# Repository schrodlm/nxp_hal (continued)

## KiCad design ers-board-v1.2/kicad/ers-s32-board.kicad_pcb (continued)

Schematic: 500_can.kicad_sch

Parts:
C30: 10uF; C_0805_2012Metric_Pad1.18x1.45mm_HandSolder; JLCPCB Part C15850
C31, C32: 100nF; C_0603_1608Metric_Pad1.08x0.95mm_HandSolder; JLCPCB Part C14663
C33, C34: 100pF; C_0603_1608Metric_Pad1.08x0.95mm_HandSolder; JLCPCB Part C14858
D4: PESD2IVN24-TR; SOT-23; Mouser 771-PESD2IVN24-TR
L2: DLW21SZ900HQ2L; L_choke_DLW21SZ; Mouser 81-DLW21SZ900HQ2L
U2: TJA1044GTK/3Z; HVSON-8-1EP_3x3mm_P0.65mm_EP1.6x2.4mm; Mouser 771-TJA1044GTK/3Z

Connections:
/CAN_S32_+: C34.1, D4.1, L2.2; also elsewhere on the board
/CAN_S32_-: C33.1, D4.2, L2.3; also elsewhere on the board
/CAN_S32_RX: U2.4 (RXD); also elsewhere on the board
/CAN_S32_STB: U2.8 (STB); also elsewhere on the board
/CAN_S32_TX: U2.1 (TXD); also elsewhere on the board
GND: C30.2, C31.2, C32.2, C33.2, C34.2, D4.3, U2.2 (GND), U2.9 (EP); also elsewhere on the board
unnamed: L2.1, U2.7 (CANH)
unnamed: L2.4, U2.6 (CANL)
VCC_3V3_CTRL: C32.1, U2.5 (VIO); also elsewhere on the board
VCC_5V_CTRL: C30.1, C31.1, U2.3 (VCC); also elsewhere on the board

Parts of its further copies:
C35: 10uF; C_0805_2012Metric_Pad1.18x1.45mm_HandSolder; JLCPCB Part C15850
C36, C37: 100nF; C_0603_1608Metric_Pad1.08x0.95mm_HandSolder; JLCPCB Part C14663
C38, C39: 100pF; C_0603_1608Metric_Pad1.08x0.95mm_HandSolder; JLCPCB Part C14858
D5: PESD2IVN24-TR; SOT-23; Mouser 771-PESD2IVN24-TR
L3: DLW21SZ900HQ2L; L_choke_DLW21SZ; Mouser 81-DLW21SZ900HQ2L
U3: TJA1044GTK/3Z; HVSON-8-1EP_3x3mm_P0.65mm_EP1.6x2.4mm; Mouser 771-TJA1044GTK/3Z

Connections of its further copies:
/CAN_STM_+: C39.1, D5.1, L3.2; also elsewhere on the board
/CAN_STM_-: C38.1, D5.2, L3.3; also elsewhere on the board
/CAN_STM_RX: U3.4 (RXD); also elsewhere on the board
/CAN_STM_STB: U3.8 (STB); also elsewhere on the board
/CAN_STM_TX: U3.1 (TXD); also elsewhere on the board
GND: C35.2, C36.2, C37.2, C38.2, C39.2, D5.3, U3.2 (GND), U3.9 (EP); also elsewhere on the board
unnamed: L3.1, U3.7 (CANH)
unnamed: L3.4, U3.6 (CANL)
VCC_3V3_DISCO: C37.1, U3.5 (VIO); also elsewhere on the board
VCC_5V_DISCO: C35.1, C36.1, U3.3 (VCC); also elsewhere on the board

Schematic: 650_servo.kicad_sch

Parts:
C43: 10uF; C_0805_2012Metric_Pad1.18x1.45mm_HandSolder; JLCPCB Part C15850
J11: SERVO; PinHeader_1x03_P2.54mm_Vertical; JLCPCB Part C2937625

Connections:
/SERVO_PWM: J11.1; also elsewhere on the board
GND: C43.2, J11.3; also elsewhere on the board
VCC_5V_PERIPH: C43.1, J11.2; also elsewhere on the board

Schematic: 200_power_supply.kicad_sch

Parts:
C4, C6: 10uF; C_0805_2012Metric_Pad1.18x1.45mm_HandSolder; JLCPCB Part C15850
C5, C7: 100nF; C_0603_1608Metric_Pad1.08x0.95mm_HandSolder; JLCPCB Part C14663
FB2: BLM18KG601SN1D; L_0603_1608Metric_Pad1.05x0.95mm_HandSolder; JLCPCB Part C85833
U1: TPS70933QDRV; WSON-6-1EP_2x2mm_P0.65mm_EP1x1.6mm; Mouser 595-TPS70933QDRVRQ1

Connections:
/200_power_supply/VCC_3V3_LDO: C6.1, C7.1, FB2.1, U1.1 (OUT)
GND: C4.2, C5.2, C6.2, C7.2, U1.3 (GND), U1.7 (GND); also elsewhere on the board
VCC_3V3: FB2.2; also elsewhere on the board
VCC_5V: C4.1, C5.1, U1.4 (EN), U1.6 (IN); also elsewhere on the board

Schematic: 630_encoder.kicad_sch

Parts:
C41, C42: 10nF; C_0603_1608Metric_Pad1.08x0.95mm_HandSolder; JLCPCB Part C57112
IC4: PEC12R-4220F-S0024; Mouser 652-PEC12R-4220F-S24
R30, R31, R32, R33, R34: 10k; R_0603_1608Metric_Pad0.98x0.95mm_HandSolder; JLCPCB Part C25804

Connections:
/ENC_A: C42.1, R31.2; also elsewhere on the board
/ENC_B: C41.1, R30.2; also elsewhere on the board
/ENC_SWITCH: IC4.S2, R34.1; also elsewhere on the board
GND: C41.2, C42.2, IC4.MP, R32.2, R33.2, R34.2; also elsewhere on the board
unnamed: IC4.A, R31.1, R32.1
unnamed: IC4.B, R30.1, R33.1
VCC_3V3_PERIPH: IC4.C, IC4.S1; also elsewhere on the board

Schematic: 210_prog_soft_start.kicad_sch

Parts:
C3: 100nF; C_0603_1608Metric_Pad1.08x0.95mm_HandSolder; JLCPCB Part C14663
D3: B5817WS; D_SOD-323; Mouser 771-PMEG4005EJ-T/R
Q1: DMG3406L; SOT-23; Mouser 621-DMG3406L-13
R9: 10k; R_0603_1608Metric_Pad0.98x0.95mm_HandSolder; Mouser 603-RC0603FR-0710KL; not fitted
R10: 10k; R_0603_1608Metric_Pad0.98x0.95mm_HandSolder; JLCPCB Part C25804

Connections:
/210_prog_soft_start/PROG_SOFT_START_GATE: C3.1, D3.2 (A), Q1.1 (G), R10.1
/PROG_USB_VBUS: D3.1 (K), R9.2, R10.2; also elsewhere on the board
/VCC_3V3_PROG_RAW: Q1.3 (D); also elsewhere on the board
GND: C3.2, R9.1; also elsewhere on the board
VCC_3V3_PROG: Q1.2 (S); also elsewhere on the board

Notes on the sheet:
This implements soft-start and disconnects VCC_3V3_SOFT if not powered by USB_VBUS (5V).
This does not seem to be needed because even the VBUS from USB does not go to 0 immediately.

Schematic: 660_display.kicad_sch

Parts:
J12: DISPLAY; PinHeader_1x08_P2.54mm_Vertical; JLCPCB Part C492407

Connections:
/MEM_DISP_SCK: J12.4; also elsewhere on the board
/MEM_DISP_SDI: J12.3; also elsewhere on the board
/~DISP_CS: J12.6; also elsewhere on the board
/~DISP_DC: J12.5; also elsewhere on the board
/~DISP_RST: J12.7; also elsewhere on the board
GND: J12.1, J12.8; also elsewhere on the board
VCC_3V3_PERIPH: J12.2; also elsewhere on the board

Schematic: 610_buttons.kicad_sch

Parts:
R24, R25, R26, R27: 10k; R_0603_1608Metric_Pad0.98x0.95mm_HandSolder; JLCPCB Part C25804
S2, S3, S4, S5: PTS815SJM250SMTR_LFS; Mouser 611-PTS815SJM250SMTR

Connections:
/BTN_1: R27.1, S2.2; also elsewhere on the board
/BTN_2: R26.1, S3.2; also elsewhere on the board
/BTN_3: R25.1, S4.2; also elsewhere on the board
/BTN_4: R24.1, S5.2; also elsewhere on the board
GND: R24.2, R25.2, R26.2, R27.2; also elsewhere on the board
VCC_3V3_PERIPH: S2.1, S3.1, S4.1, S5.1; also elsewhere on the board

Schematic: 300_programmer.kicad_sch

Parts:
C8: 10uF; C_0805_2012Metric_Pad1.18x1.45mm_HandSolder; JLCPCB Part C15850
C9, C19: 22uF; C_0805_2012Metric_Pad1.18x1.45mm_HandSolder; JLCPCB Part C45783
C10, C11, C12, C13, C14, C15, C16, C17: 100nF; C_0603_1608Metric_Pad1.08x0.95mm_HandSolder; JLCPCB Part C14663
C18: 47pF; C_0603_1608Metric_Pad1.08x0.95mm_HandSolder; JLCPCB Part C1671
C20, C21: 8pF; C_0603_1608Metric_Pad1.08x0.95mm_HandSolder; JLCPCB Part C36508
IC1: LPC55S69JBD64K; Mouser 771-LPC55S69JBD64K
L1: 4u7H; LCD0805; JLCPCB Part C395016
R11, R12: 10k; R_0603_1608Metric_Pad0.98x0.95mm_HandSolder; Mouser 603-RC0603FR-0710KL; not fitted
R13, R14: 0R; R_0603_1608Metric_Pad0.98x0.95mm_HandSolder; Mouser 603-RC0603FR-100RL; not fitted
Y1: 3225-16-8-10-10/A; 3225-16-8-10-10_A; JLCPCB Part C2981656

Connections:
/300_programmer/CLK_N: C20.1, IC1.19 (XTAL32M_N), Y1.1
/300_programmer/CLK_P: C21.1, IC1.20 (XTAL32M_P), Y1.3
/300_programmer/HW_VER_6: IC1.38 (PIO0_18/ACMP0_C), R11.2, R13.1
/300_programmer/HW_VER_7: IC1.18 (PIO0_27), R12.2, R14.1
/300_programmer/USB1_VBUS: IC1.25 (USB1_VBUS); also elsewhere on the board
/PROG_ISP_EN_LED_CTRL: IC1.56 (PIO0_5/TDI); also elsewhere on the board
/PROG_RESETN: IC1.21 (RESETN); also elsewhere on the board
/PROG_SWCLK: IC1.6 (PIO0_11/ADC0_9); also elsewhere on the board
/PROG_SWDIO: IC1.5 (PIO0_12/ADC0_10); also elsewhere on the board
/PROG_SWO: IC1.13 (PIO0_10/ADC0_1); also elsewhere on the board
/PROG_USB_D+: IC1.23 (USB1_DP); also elsewhere on the board
/PROG_USB_D-: IC1.24 (USB1_DM); also elsewhere on the board
/TARGET_DEBUG_RX: IC1.51 (PIO0_25); also elsewhere on the board
/TARGET_DEBUG_TX: IC1.45 (PIO0_24); also elsewhere on the board
/TARGET_RESETN: IC1.58 (PIO0_19); also elsewhere on the board
/TARGET_SWCLK: IC1.36 (PIO0_0/ACMP0_A); also elsewhere on the board
/TARGET_SWDIO: IC1.52 (PIO0_2/TRST); also elsewhere on the board
/TARGET_SWO: IC1.53 (PIO0_3/TCK); also elsewhere on the board
GND: C8.2, C9.2, C10.2, C11.2, C12.2, C13.2, C14.2, C15.2, C16.2, C17.2, C18.2, C19.2, C20.2, C21.2, IC1.11 (VSSA), IC1.22 (USB1_VSS), IC1.26 (USB1_VSS), IC1.30 (VSS_DCDC), IC1.37 (PIO0_9/ACMP0_B), IC1.64 (USB0_VSS), IC1.65 (EP), R13.2, R14.2, Y1.2, Y1.4; also elsewhere on the board
unnamed: C19.1, IC1.28 (VDD_PMU), IC1.29 (FB), L1.1
unnamed: IC1.31 (LX), L1.2
VCC_3V3_PROG: C8.1, C9.1, C10.1, C11.1, C12.1, C13.1, C14.1, C15.1, C16.1, C17.1, C18.1, IC1.8 (VDD), IC1.9 (VDDA), IC1.10 (VREFP), IC1.15 (PIO0_31/ADC0_3), IC1.16 (VDD), IC1.27 (USB1_3V3), IC1.32 (VBAT_DCDC), IC1.33 (VBAT_PMU), IC1.43 (VDD), IC1.54 (VDD), IC1.61 (USB0_3V3), R11.1, R12.1; also elsewhere on the board

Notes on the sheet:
Connect to GND: Disable second VCOM
SWD debug disabled when low Presumably has internal pull-up
VCOM disabled when low Presumably has internal pull-up

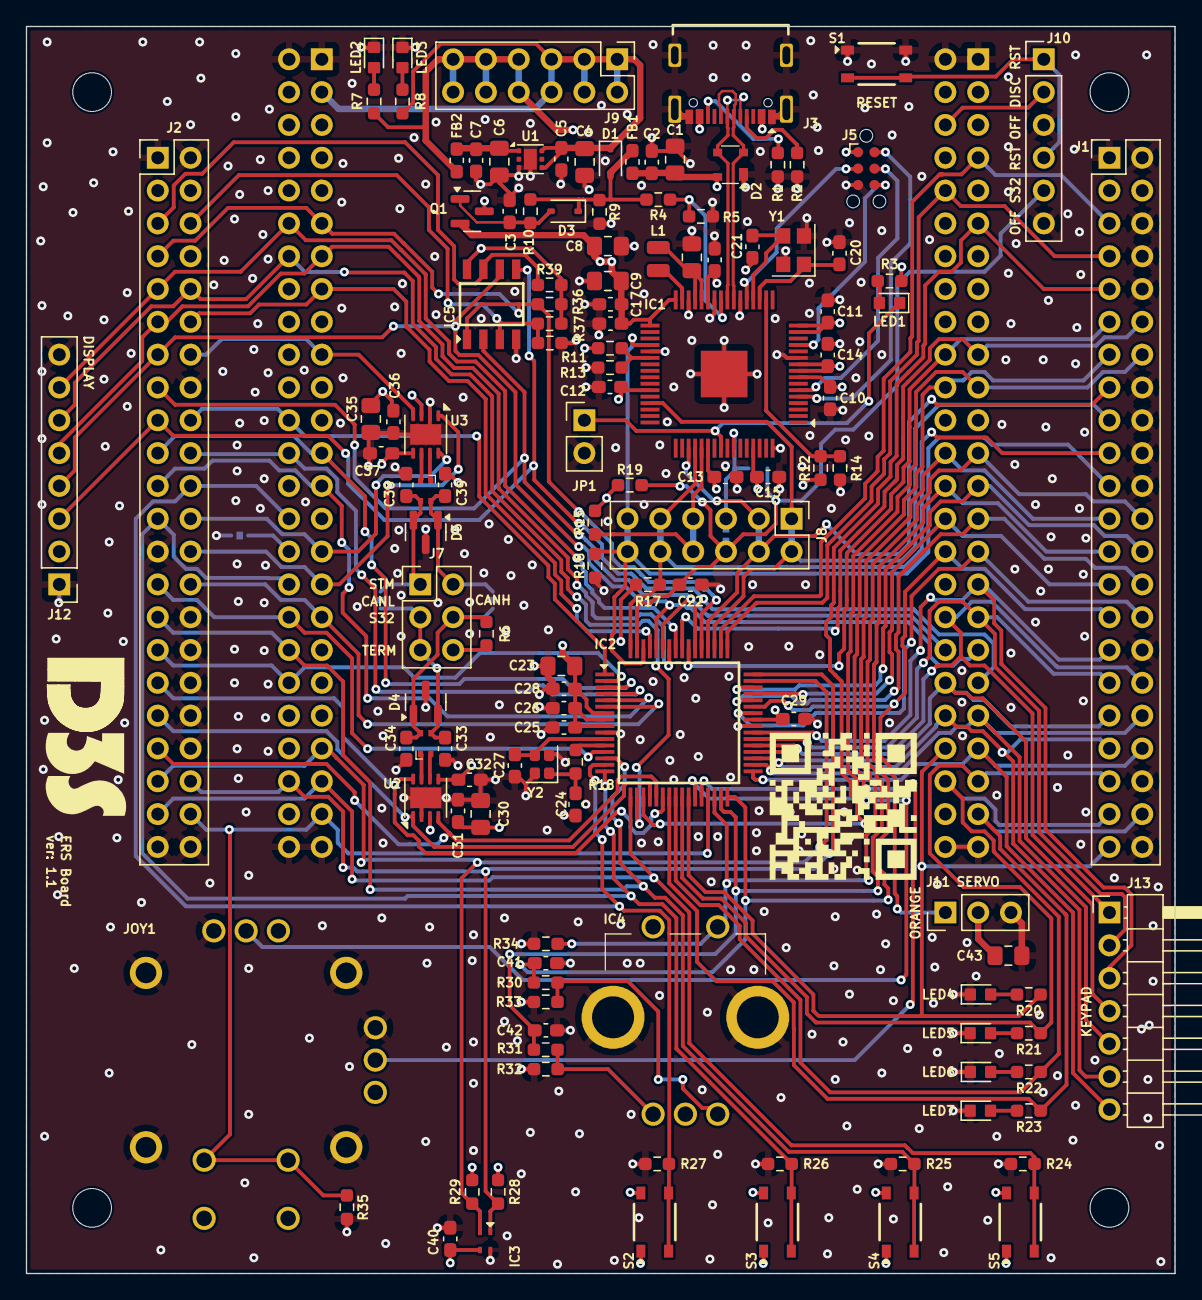
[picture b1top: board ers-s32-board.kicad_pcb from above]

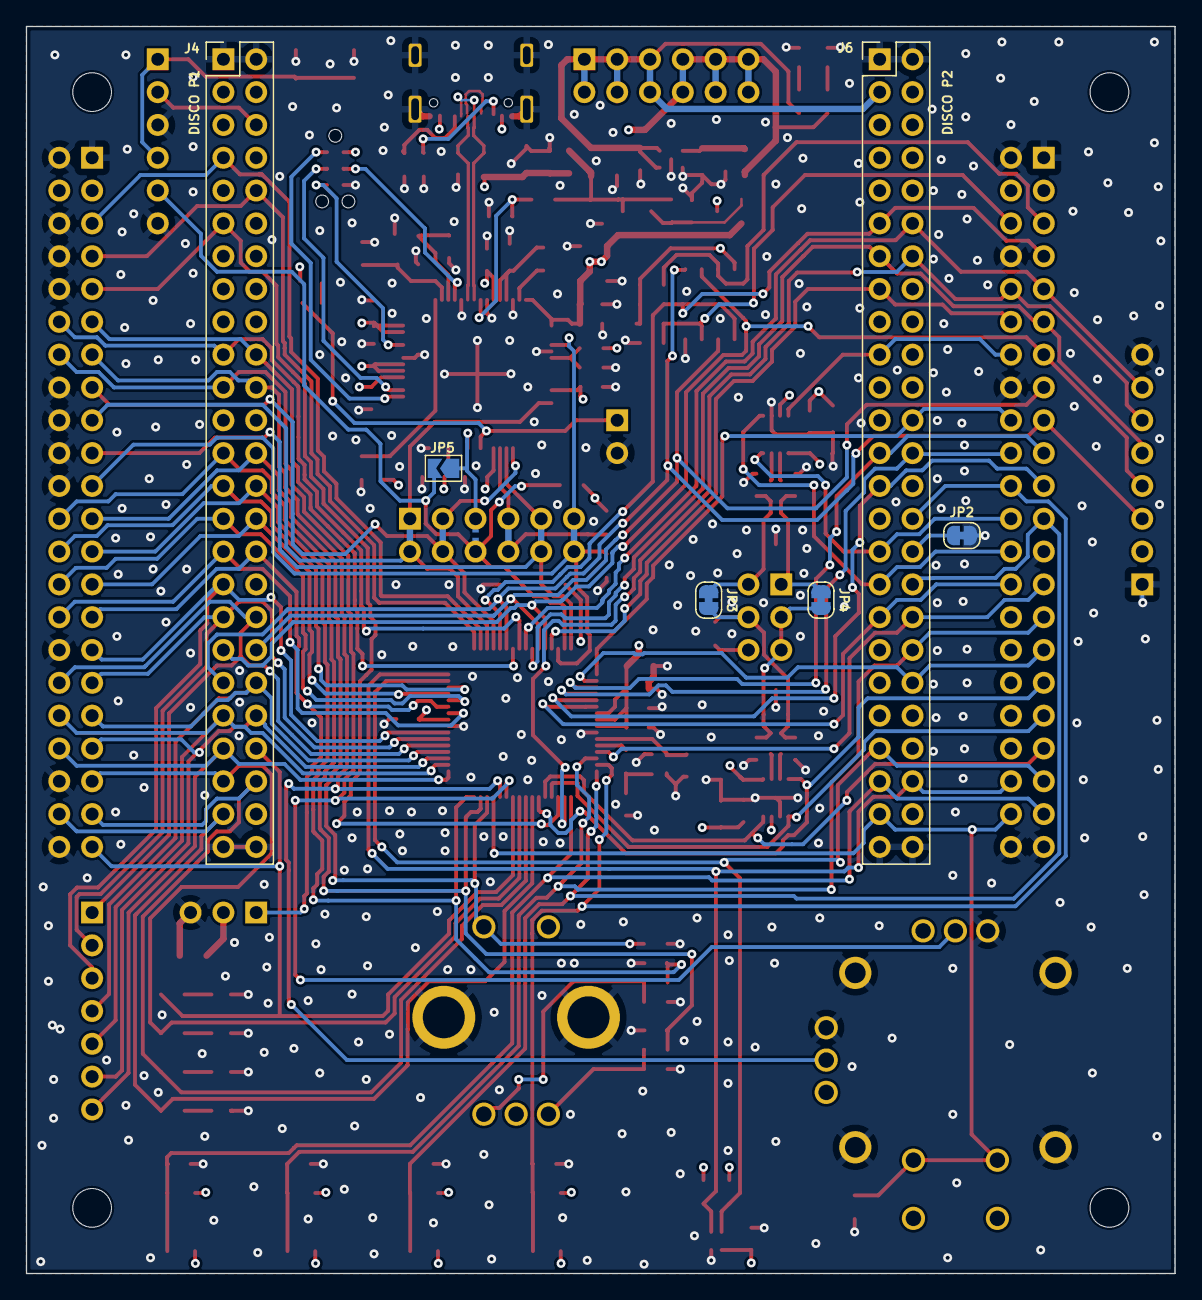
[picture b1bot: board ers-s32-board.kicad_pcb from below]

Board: 4 copper layers, 88.9 x 96.5 mm, 138 parts (6 on the bottom side), 123 nets.

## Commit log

2026-06-07 Init project
2026-06-07 Update gitignore
2026-06-07 Provide setup script
2026-06-07 Fix build script
2026-06-07 Add clangd setup
2026-06-07 Introduce clang format
2026-06-07 [5-1] Implement led HAL
2026-06-07 [5-2] Add BTN HAL
2026-06-07 Add LED HAL docs
2026-06-08 [5-3] Implement btn_cnt FSM
2026-06-08 [5-4] Implement kpad hal
2026-06-08 [5-5] Implement encoder hal
2026-06-08 [5-6] Implement servo HAL
2026-06-13 [5-7] Implement blocking SPI HAL
2026-06-13 Update clangd
2026-06-13 [5-7] Implement LCD HAL
2026-06-14 [5-8] Implement EEPROM
2026-06-14 Add vscode launch config
2026-06-14 [5-8] SPI handling multibyte transfers
2026-06-14 [5-9] Implement joystick API
2026-06-14 [5-10] Implement humidity sensor (and I2C)
